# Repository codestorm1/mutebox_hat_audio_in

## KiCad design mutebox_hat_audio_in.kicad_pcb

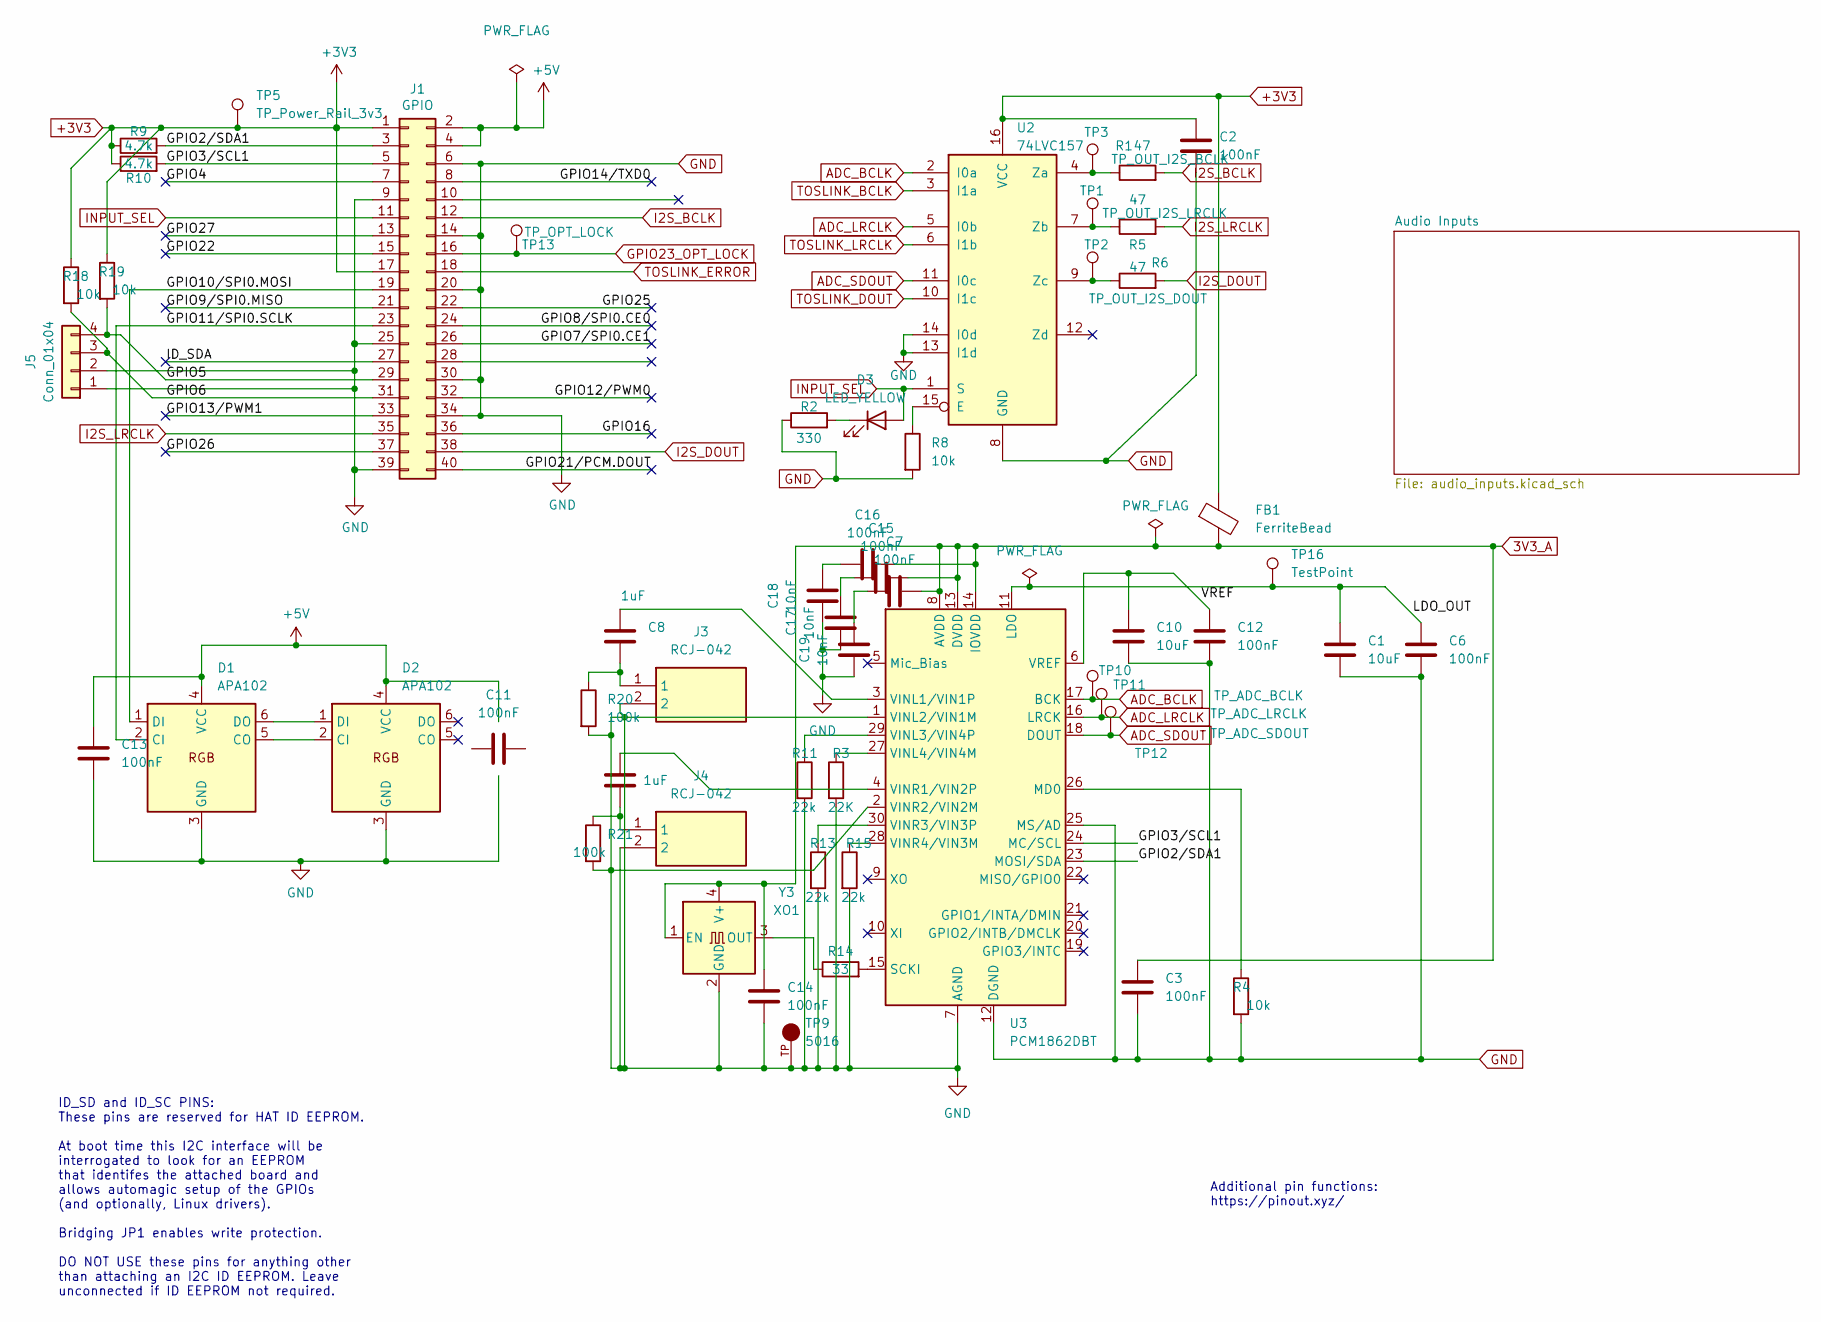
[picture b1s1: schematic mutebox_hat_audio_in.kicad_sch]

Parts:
C1, C10: 10uF; C_0402_1005Metric; LCSC C440198
C2, C3: 100nF; C_0805_2012Metric; LCSC C17414
C6, C7, C12, C15, C16: 100nF; C_0402_1005Metric; LCSC C1525
C8: 1uF; C_0402_1005Metric; LCSC C14445
C9: 1uF; C_0805_2012Metric; LCSC C14445
C11, C13: 100nF; C_0805_2012Metric; LCSC C1711
C14: 100nF; C_0402_1005Metric
C17, C18, C19: 10nF; C_0402_1005Metric; LCSC C15195
D1, D2: APA102; LED_RGB_5050-6; LCSC C5378730
D3: LED_YELLOW; LED_0402_1005Metric; LCSC C136118
FB1: FerriteBead; L_0805_2012Metric_Pad1.05x1.20mm_HandSolder; LCSC C85840
J1: GPIO; PinSocket_2x20_P2.54mm_Vertical
J3, J4: RCJ-042; CUI_RCJ-042; Manufacturer_Part_Number RCJ-042; Mouser Part Number 490-RCJ-042
J5: Conn_01x04; PinHeader_1x04_P2.54mm_Vertical
R1, R5, R6: 47; R_0402_1005Metric; LCSC C413056
R2: 330; R_0805_2012Metric; LCSC C17471
R3: 22K; R_0402_1005Metric; LCSC C2909337
R4, R8: 10k; R_0805_2012Metric; LCSC C17414
R9, R10: 4.7k; R_0805_2012Metric; LCSC C17673
R11, R13, R15: 22k; R_0402_1005Metric; LCSC C2909337
R14: 33; R_0402_1005Metric; LCSC C17634
R18, R19: 10k; R_0402_1005Metric; LCSC C17414
R20, R21: 100k; R_0402_1005Metric; LCSC C149504
TP1: TP_OUT_I2S_LRCLK; TestPoint_Pad_D1.0mm
TP2: TP_OUT_I2S_DOUT; TestPoint_Pad_D1.0mm
TP3: TP_OUT_I2S_BCLK; TestPoint_Pad_D1.0mm
TP5: TP_Power_Rail_3v3; TestPoint_Pad_D1.0mm
TP9: 5016; KEYSTONE_5016; PARTREV D
TP10: TP_ADC_BCLK; TestPoint_Pad_D1.0mm
TP11: TP_ADC_LRCLK; TestPoint_Pad_D1.0mm
TP12: TP_ADC_SDOUT; TestPoint_Pad_D1.0mm
TP13: TP_OPT_LOCK; TestPoint_Pad_D1.0mm
TP16: TestPoint; TestPoint_Pad_D1.0mm
U2: 74LVC157; SOIC-16_3.9x9.9mm_P1.27mm; LCSC C7664
U3: PCM1862DBT; DBT0030A_N; LCSC C544647
Y3: XO1; Oscillator_SMD_EuroQuartz_XO32-4Pin_3.2x2.5mm; LCSC C6159263

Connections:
3V3_A: C3.1, C7.2, C14.1, C15.2, C16.2, FB1.2, U3.8 (AVDD), U3.13 (DVDD), U3.14 (IOVDD), Y3.1 (EN), Y3.4 (V+)
+3V3: C2.1, FB1.1, J1.1, J1.17, R9.1, R10.1, R18.1, R19.1, TP5.1, U2.16 (VCC); also elsewhere on the board
+5V: C13.1, D1.4 (VCC), D2.4 (VCC), J1.2, J1.4
/GPIO2/SDA1: J1.3, R9.2, U3.23 (MOSI/SDA)
/GPIO3/SCL1: J1.5, R10.2, U3.24 (MC/SCL)
/GPIO4: J1.7
/GPIO5: J1.29, J5.4, R19.2
/GPIO6: J1.31, J5.3, R18.2
/GPIO7/SPI0.CE1: J1.26
/GPIO8/SPI0.CE0: J1.24
/GPIO9/SPI0.MISO: J1.21
/GPIO10/SPI0.MOSI: D1.1 (DI), J1.19
/GPIO11/SPI0.SCLK: D1.2 (CI), J1.23
/GPIO12/PWM0: J1.32
/GPIO13/PWM1: J1.33
/GPIO14/TXD0: J1.8
/GPIO16: J1.36
/GPIO21/PCM.DOUT: J1.40
/GPIO22: J1.15
/GPIO25: J1.22
/GPIO26: J1.37
/GPIO27: J1.13
/ID_SDA: J1.27
/LDO_OUT: C1.1, C6.1, TP16.1, U3.11 (LDO)
/VREF: C10.1, C12.1, U3.6 (VREF)
ADC_BCLK: TP10.1, U2.2 (I0a), U3.17 (BCK)
ADC_LRCLK: TP11.1, U2.5 (I0b), U3.16 (LRCK)
ADC_SDOUT: TP12.1, U2.11 (I0c), U3.18 (DOUT)
GND: C1.2, C2.2, C3.2, C6.2, C10.2, C12.2, C13.2, C14.2, C17.2, C18.2, C19.2, D1.3 (GND), D2.3 (GND), J1.6, J1.9, J1.14, J1.20, J1.25, J1.30, J1.34, J1.39, J3.2, J4.2, J5.1, J5.2, R2.1, R3.2, R4.2, R8.2, R11.2, R13.2, R15.2, R20.2, R21.2, TP9.TP, U2.8 (GND), U2.13 (I1d), U2.14 (I0d), U3.1 (VINL2/VIN1M), U3.2 (VINR2/VIN2M), U3.7 (AGND), U3.12 (DGND), U3.25 (MS/AD), Y3.2 (GND); also elsewhere on the board
GPIO23_OPT_LOCK: J1.16, TP13.1; also elsewhere on the board
I2S_BCLK: J1.12, R1.2
I2S_DOUT: J1.38, R6.2
I2S_LRCLK: J1.35, R5.2
INPUT_SEL: D3.2 (A), J1.11, U2.1 (S)
unnamed: C8.2, J3.1, R20.1
unnamed: C9.2, J4.1, R21.1
unnamed: C15.1, C17.1
unnamed: C16.1, C18.1
unnamed: C7.1, C19.1
unnamed: D1.5 (CO), D2.2 (CI)
unnamed: D1.6 (DO), D2.1 (DI)
unnamed: D3.1 (K), R2.2
unnamed: R8.1, U2.15 (E)
unnamed: R1.1, TP3.1, U2.4 (Za)
unnamed: R5.1, TP1.1, U2.7 (Zb)
unnamed: R6.1, TP2.1, U2.9 (Zc)
unnamed: R4.1, U3.26 (MD0)
unnamed: R14.2, U3.15 (SCKI)
unnamed: C8.1, U3.3 (VINL1/VIN1P)
unnamed: R11.1, U3.29 (VINL3/VIN4P)
unnamed: R3.1, U3.27 (VINL4/VIN4M)
unnamed: C9.1, U3.4 (VINR1/VIN2P)
unnamed: R13.1, U3.30 (VINR3/VIN3P)
unnamed: R15.1, U3.28 (VINR4/VIN3M)
unnamed: R14.1, Y3.3 (OUT)
TOSLINK_BCLK: U2.3 (I1a); also elsewhere on the board
TOSLINK_DOUT: U2.10 (I1c); also elsewhere on the board
TOSLINK_ERROR: J1.18; also elsewhere on the board
TOSLINK_LRCLK: U2.6 (I1b); also elsewhere on the board

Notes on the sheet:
Additional pin functions: https://pinout.xyz/
ID_SD and ID_SC PINS: These pins are reserved for HAT ID EEPROM. At boot time this I2C interface will be interrogated to look for an EEPROM that identifes the attached board and allows automagic setup of the GPIOs (and optionally, Linux drivers). Bridging JP1 enables write protection. DO NOT USE th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

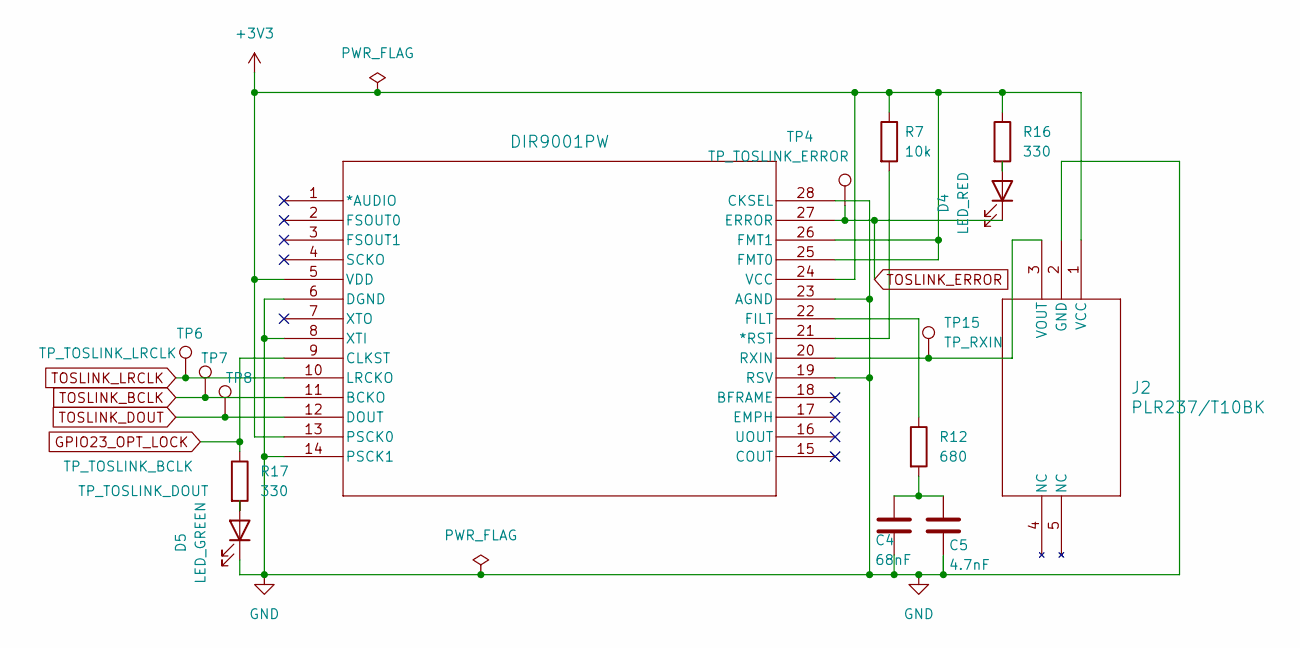
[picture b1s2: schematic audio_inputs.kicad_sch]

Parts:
C4: 68nF; C_0805_2012Metric; LCSC C107159
C5: 4.7nF; C_0805_2012Metric; LCSC C1744
D4: LED_RED; LED_0402_1005Metric; LCSC C71911
D5: LED_GREEN; LED_0402_1005Metric; LCSC C74338
J2: PLR237/T10BK; PLR237T10BK
R7: 10k; R_0805_2012Metric; LCSC C17414
R12: 680; R_0402_1005Metric; LCSC C156168
R16, R17: 330; R_0402_1005Metric; LCSC C1705212
TP4: TP_TOSLINK_ERROR; TestPoint_Pad_D1.0mm
TP6: TP_TOSLINK_LRCLK; TestPoint_Pad_D1.0mm
TP7: TP_TOSLINK_BCLK; TestPoint_Pad_D1.0mm
TP8: TP_TOSLINK_DOUT; TestPoint_Pad_D1.0mm
TP15: TP_RXIN; TestPoint_Pad_D1.0mm
U5: DIR9001PW; PW28-M; LCSC C96215

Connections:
+3V3: J2.1 (VCC), R7.1, R16.1, U5.5 (VDD), U5.13 (PSCK0), U5.24 (VCC), U5.25 (FMT0), U5.26 (FMT1); also elsewhere on the board
GND: C4.2, C5.2, D5.1 (K), J2.2 (GND), U5.6 (DGND), U5.8 (XTI), U5.14 (PSCK1), U5.19 (RSV), U5.23 (AGND), U5.28 (CKSEL); also elsewhere on the board
GPIO23_OPT_LOCK: R17.1, U5.9 (CLKST); also elsewhere on the board
unnamed: C4.1, C5.1, R12.2
unnamed: D4.2 (A), R16.2
unnamed: D5.2 (A), R17.2
unnamed: J2.3 (VOUT), TP15.1, U5.20 (RXIN)
unnamed: R7.2, U5.21 (*RST)
unnamed: R12.1, U5.22 (FILT)
TOSLINK_BCLK: TP7.1, U5.11 (BCKO); also elsewhere on the board
TOSLINK_DOUT: TP8.1, U5.12 (DOUT); also elsewhere on the board
TOSLINK_ERROR: D4.1 (K), TP4.1, U5.27 (ERROR); also elsewhere on the board
TOSLINK_LRCLK: TP6.1, U5.10 (LRCKO); also elsewhere on the board

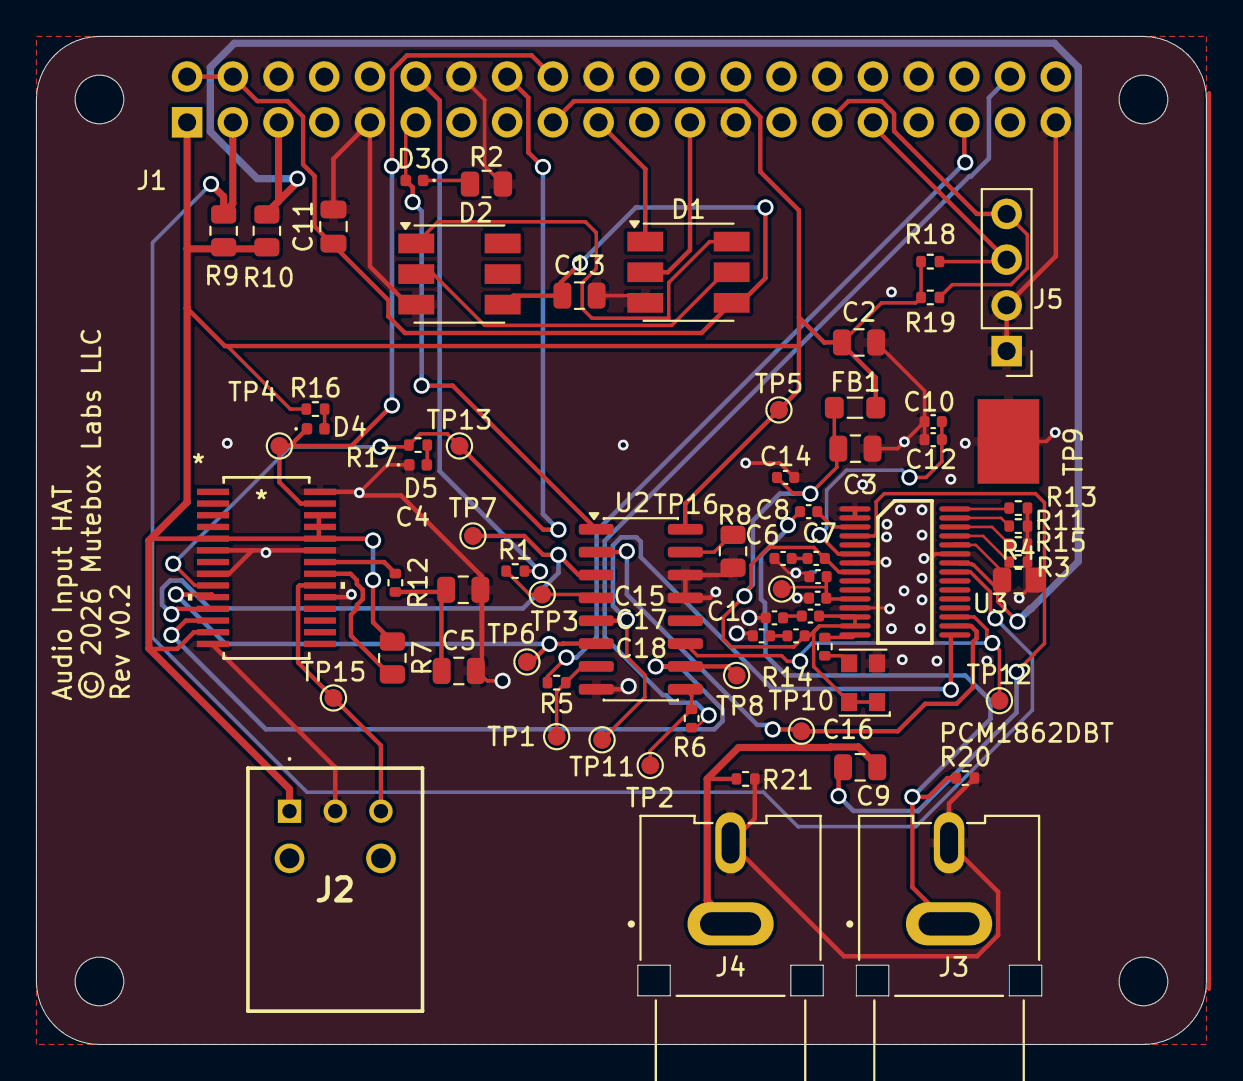
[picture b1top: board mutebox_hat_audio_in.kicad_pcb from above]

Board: 2 copper layers, 65.0 x 56.0 mm, 74 parts (1 on the bottom side), 51 nets.

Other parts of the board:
MH1, MH2, MH3, MH4: MountingHole_2.7mm_M2.5

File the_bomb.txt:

BEFORE ORDERING:

run ERC Electric Rules Checker

run DRC Design Rules Checker

"Designator","Value","Datasheet","Footprint","Qty","DNP","LCSC Part Number"
"C1,C10","10uF","~","Capacitor_SMD:C_0402_1005Metric","2","","C440198"
"C2,C3,C6,C7,C11,C12,C13,C14,C15,C16","100nF","~","Capacitor_SMD:C_0402_1005Metric,Capacitor_SMD:C_0805_2012Metric_Pad1.18x1.45mm_HandSolder","10","","C1525,C49678"
"C4","68nF","~","Capacitor_SMD:C_0805_2012Metric_Pad1.18x1.45mm_HandSolder","1","","C107159"
"C5","4.7nF","~","Capacitor_SMD:C_0805_2012Metric_Pad1.18x1.45mm_HandSolder","1","","C1744"
"C8,C9","1uF","~","Capacitor_SMD:C_0402_1005Metric,Capacitor_SMD:C_0805_2012Metric_Pad1.18x1.45mm_HandSolder","2","","C28323"
"C17,C18,C19","10nF","~","Capacitor_SMD:C_0402_1005Metric","3","","C15195"
"D1,D2","APA102","https://cdn-shop.adafruit.com/product-files/2343/APA102C.pdf","LED_SMD:LED_RGB_5050-6","2","","C5378730"
"D3","NCD0805R1","~","Capacitor_SMD:C_0402_1005Metric","1","","C2971978"
"FB1","FerriteBead","~","Inductor_SMD:L_0805_2012Metric_Pad1.05x1.20mm_HandSolder","1","","C85840"
"R1,R5,R6","47","~","Resistor_SMD:R_0402_1005Metric","3","","C413056"
"R2","330","~","Resistor_SMD:R_0805_2012Metric_Pad1.20x1.40mm_HandSolder","1","","C17471"
"R3","22K","~","Resistor_SMD:R_0402_1005Metric","1","","C2909337"
"R4,R7,R8","10k","~","Resistor_SMD:R_0402_1005Metric,Resistor_SMD:R_0805_2012Metric_Pad1.20x1.40mm_HandSolder","3","","C17414"
"R9,R10","4.7k","~","Resistor_SMD:R_0805_2012Metric_Pad1.20x1.40mm_HandSolder","2","","C17673"
"R11,R13,R15","22k","~","Resistor_SMD:R_0402_1005Metric","3","","C2909337"
"R12","680","~","Resistor_SMD:R_0805_2012Metric_Pad1.20x1.40mm_HandSolder","1","","C156168"
"R14","33","~","Resistor_SMD:R_0402_1005Metric","1","","C17634"
"R20,R21","100k","~","Resistor_SMD:R_0805_2012Metric_Pad1.20x1.40mm_HandSolder","2","","C149504"
"TP9","5016","","Connector:KEYSTONE_5016","1","",""
"TP16","TestPoint","~","TestPoint:TestPoint_Pad_D1.0mm","1","",""
"U2","74LVC157","http://www.ti.com/lit/gpn/sn74LS157","Package_SO:SOIC-16_3.9x9.9mm_P1.27mm","1","","C7664"
"U3","PCM1862DBT","https://www.ti.com/lit/ds/symlink/pcm1862.pdf","PCM1862DBT:DBT0030A_N","1","","C544647"
"U5","DIR9001PW","https://www.ti.com/lit/gpn/dir9001","DIR9001_newfoot:PW28-M","1","","C96215"
"Y3","XO1","https://www.lcsc.com/datasheet/C6159263.pdf","Oscillator:Oscillator_SMD_EuroQuartz_XO32-4Pin_3.2x2.5mm","1","","C6159263"

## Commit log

2025-12-30 Added WM8804 SPDIF support board.
2025-12-30 Added PWR_FLAGs. Fixed some issues
2025-12-30 schematic fixes
2026-01-02 Some cleanup of schematic symbols etc.
2026-01-03 Added footprint assignments
2026-01-03 Changes to footprints (?)
2026-01-04 switched to DIR9001PW for digital audio input
2026-01-04 visiually cleaned up DIR9000
2026-01-04 Fixed some errors, like power connections
2026-01-05 Fixed some connections and global labels
2026-01-05 Fixed power/caps for TOSLINK. Got ERC down to warnings
2026-01-05 Assigned footprints that were missing
2026-01-05 Small tweaks, positioning. About to start PCB
2026-01-05 Started on PCB
2026-01-05 Started positioning of components
2026-01-05 Laid out most components
2026-01-05 Added SPDIF/TOSLINK footprint
2026-01-05 Added new footprints for TOSLINK and RCA. Fixed outer edge. PCB ready to add routes.
2026-01-07 Added routes for crystal and part of toslink
2026-01-07 Got ground layers/fill zones done
2026-01-07 Added 3v3_a traces. rearranged some components
2026-01-08 Added trace routes/vias on the Back Copper plane
2026-01-09 Ran vias to back panel for connections. Fixed all DRC errors
2026-01-09 Small route fixes
2026-01-10 Added better multiplexer setup
2026-01-10 Changed DIN connections
2026-01-11 Fixed a bunch of schematic issues
2026-01-11 More fixes
2026-01-11 More routing on PCB
2026-01-11 Fixed all routes but TOSLINK footprint
2026-01-11 More route cleanup on PCB
2026-01-11 Fixed footprint for ADC chip (PCM1862). Fixed more issues.
2026-01-12 Added symbol and footprint for PLR237/T10BK Toslink
2026-01-12 Fixed RCA Jack symbols and footprints
2026-01-12 fixed cooper fill zone issue. Fixed broken routes
2026-01-12 PCB tweaks
2026-01-13 Fixed all DRC errors
2026-02-04 Fixed inconsistencies in footprints and names
2026-02-07 Replaced footprint for DIR9001PW
2026-02-07 Removed unneeded crystal for DIR9001PW
2026-02-09 Updated schematic with correct symbol for DIR9001PW
2026-02-09 Progress updating to correct footprint for DIR9001PW chip
2026-02-09 Fixed problems with zone fills and general PCB hell
2026-02-10 kinda broken
2026-02-11 Fixed remaining issues. Sent to production house
2026-02-12 Fixed 620 ohm resistor to 680. Added parts for dotstart lights. Added LCSC part numbers to components
2026-02-28 minor changes. Rev 0.1a in a recent build
2026-02-28 Fixed traves on oscillator
2026-02-28 Added testpoint with large clip on footprint
2026-03-01 Fixed dotstar positioning. Minor changes to PCB
2026-03-01 Dlete DS Store
2026-03-01 Added LED for OPT LOCK
2026-03-01 Rewired MS to 3v3a instead of GND
2026-03-01 Fixed PCB for MODE_MS
2026-03-01 Moved dotstar caps to front of board.
2026-03-02 Fixed RCA Jack LCSC part numbers
2026-03-02 Final changes before ordering.
2026-03-03 Starting on version v0.1c
2026-03-03 Fixed missing connection from RPi4 to dotstar LED
2026-03-12 Fixed unconnected trace
2026-03-13 Changed MS/AD (pin 25) to go to GND for default address 0x4A
2026-03-13 Running pins 27-30 to ground through 100k resistors
2026-03-14 Added small LEDs for DIR lock status/error
2026-03-15 Cleaned up a lot around the PCM1862. ADC side looking pretty good
2026-03-15 Removed 3v3 rail going across the board. Rotated dotstars to put pin 1 upper left.
2026-03-15 Fixed DRC issues
2026-03-15 Board fixes. Nearly ready for a production test run
2026-03-15 Filled zones
2026-03-16 Final changes for production run

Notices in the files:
mutebox_hat_audio_in.kicad_pcb:
© 2026 Mutebox Labs LLC
